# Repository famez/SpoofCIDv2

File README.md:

Project forked from https://github.com/spoofcid/spoofcid

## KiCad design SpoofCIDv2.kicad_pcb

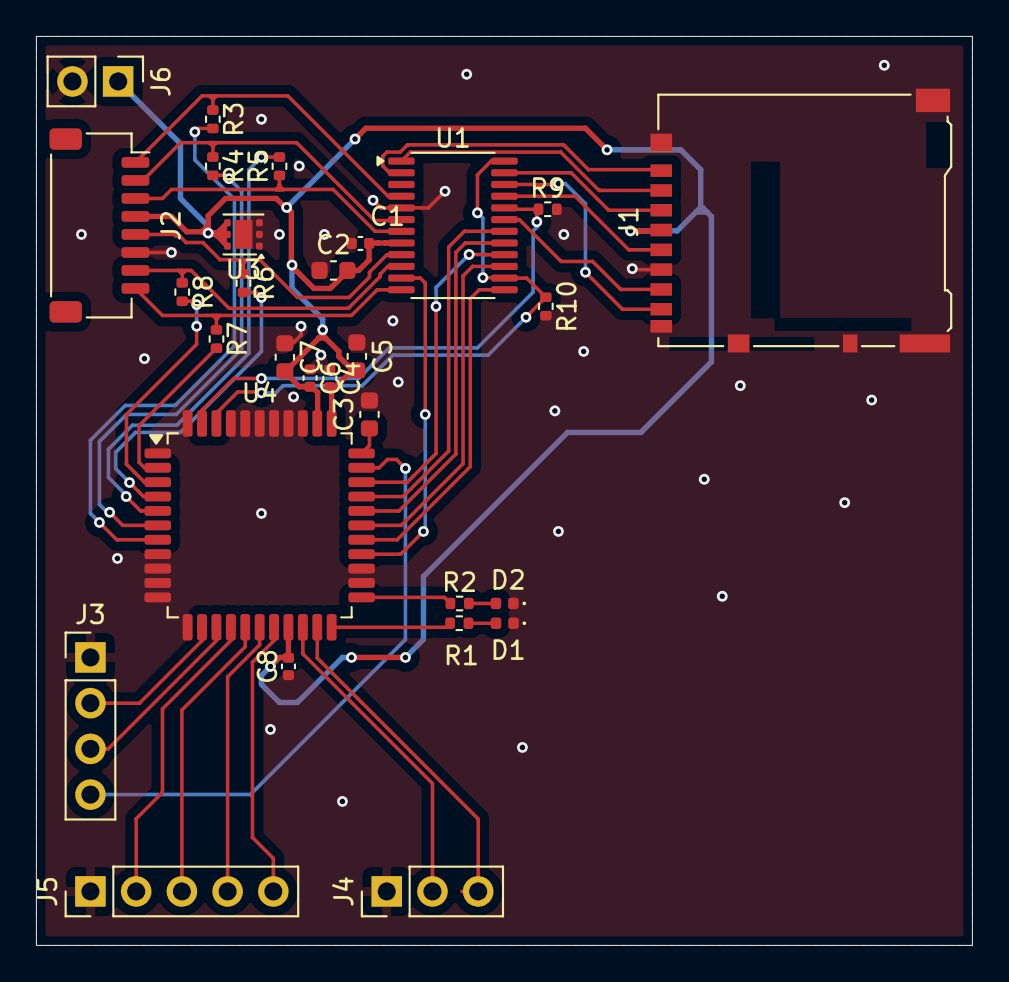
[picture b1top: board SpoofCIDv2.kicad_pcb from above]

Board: 2 copper layers, 52.0 x 50.5 mm, 29 parts (0 on the bottom side), 42 nets.

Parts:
C1, C4, C6, C8: 0.1u; C_0402_1005Metric
C2, C5, C7: 2.2u; C_0603_1608Metric
C3: 1.5u; C_0603_1608Metric
D1: GREEN LED; LED_0402_1005Metric
D2: RED LED; LED_0402_1005Metric
J1: Micro_SD_Card; microSD_HC_Hirose_DM3AT-SF-PEJM5
J2: Conn_01x08; JST_SH_SM08B-SRSS-TB_1x08-1MP_P1.00mm_Horizontal
J3: Conn_01x04_Pin; PinHeader_1x04_P2.54mm_Vertical
J4: Conn_01x03_Pin; PinHeader_1x03_P2.54mm_Vertical
J5: Conn_01x05_Pin; PinHeader_1x05_P2.54mm_Vertical
J6: Conn_01x02_Pin; PinHeader_1x02_P2.54mm_Vertical
R1, R3, R4, R5, R6, R7, R8: 100; R_0402_1005Metric
R2: 220; R_0402_1005Metric
R9, R10: 10k; R_0402_1005Metric
U1: TS3A27518EPW; TSSOP-24_4.4x7.8mm_P0.65mm
U3: TVS0500DRV; WSON-6-1EP_2x2mm_P0.65mm_EP1x1.6mm
U4: TQFP-44_10x10mm_P0.8mm

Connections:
+3.3V: C1.2, C2.2, C4.2, C5.2, C6.2, C7.2, C8.2, J1.4 (VDD), J2.4, J6.1, U1.8 (VCC), U3.4 (IN), U3.5 (IN), U3.6 (IN), U4.19 (VDDD), U4.34 (VDDD), U4.35 (VDDA)
/CARD_CLK: J1.5 (CLK), U1.21 (NC4)
/CARD_CMD: J1.3 (CMD), U1.23 (NC3)
/CARD_DAT0: J1.7 (DAT0), U1.19 (NC5)
/CARD_DAT1: J1.8 (DAT1), U1.22 (NC6)
/CARD_DAT2: J1.1 (DAT2), U1.2 (NC1)
/CARD_DAT3: J1.2 (DAT3/CD), U1.1 (NC2)
/HOST_CLK: J2.5, R6.1, U1.9 (COM4)
/HOST_CMD: J2.3, R5.1, U1.7 (COM3)
/HOST_DAT0: J2.7, R8.1, U1.10 (COM5)
/HOST_DAT1: J2.8, R7.1, U1.12 (COM6)
/HOST_DAT2: J2.1, R3.1, U1.4 (COM1)
/HOST_DAT3: J2.2, R4.1, U1.6 (COM2)
/PSOC_CLK: U1.17 (NO4), U4.29 (P0.5)
/PSOC_CMD: U1.15 (NO3), U4.28 (P0.4)
/PSOC_DAT0: U1.18 (NO5), U4.30 (P0.6)
/PSOC_DAT1: U1.16 (NO6), U4.31 (P0.7)
/PSOC_DAT2: U1.11 (NO1), U4.26 (P0.2)
/PSOC_DAT3: U1.13 (NO2), U4.27 (P0.3)
/SWDCLK: J3.3, U4.14 (P3.3)
/SWDIO: J3.2, U4.13 (P3.2)
/UART_RX: J4.2, U4.20 (P4.0)
/UART_TX: J4.3, U4.21 (P4.1)
/XRESET: J3.4, U4.32 (XRES)
GND: C1.1, C2.1, C3.2, C4.1, C5.1, C6.1, C7.1, C8.1, D1.1 (K), D2.1 (K), J1.6 (VSS), J1.9 (SHIELD), J1.10, J1.11, J2.6, J3.1, J4.1, J5.1, J6.2, R9.2, R10.2, U1.5 (GND), U3.1 (GND), U3.2 (GND), U3.3 (GND), U3.7 (GND), U4.1 (VSS), U4.8 (P2.6), U4.9 (P2.7), U4.10 (VSS), U4.11 (P3.0), U4.12 (P3.1), U4.24 (P0.0), U4.25 (P0.1), U4.36 (VSSA), U4.37 (P1.0), U4.38 (P1.1), U4.39 (P1.2), U4.40 (P1.3), U4.41 (P1.4), U4.44 (P1.7)
unnamed: D1.2 (A), R1.2
unnamed: D2.2 (A), R2.2
unnamed: J5.2, U4.15 (P3.4)
unnamed: J5.3, U4.16 (P3.5)
unnamed: J5.4, U4.17 (P3.6)
unnamed: J5.5, U4.18 (P3.7)
unnamed: R10.1, U1.14 (IN2), U1.24 (IN1), U4.42 (P1.5)
unnamed: R9.1, U1.20 (~EN), U4.43 (P1.6)
unnamed: R7.2, U4.2 (P2.0)
unnamed: R8.2, U4.3 (P2.1)
unnamed: R6.2, U4.4 (P2.2)
unnamed: R5.2, U4.5 (P2.3)
unnamed: R4.2, U4.6 (P2.4)
unnamed: R3.2, U4.7 (P2.5)
unnamed: R1.1, U4.22 (P4.2)
unnamed: R2.1, U4.23 (P4.3)
unnamed: C3.1, U4.33 (VCCD)

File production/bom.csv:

Designator,Footprint,Quantity,Value,LCSC Part #
"C1, C4, C6, C8",0402,4,0.1u,
"C2, C5, C7",0603,3,2.2u,
C3,0603,1,1.5u,
D1,0402,1,GREEN LED,
D2,0402,1,RED LED,
J1,microSD_HC_Hirose_DM3AT-SF-PEJM5,1,Micro_SD_Card,
J2,JST_SH_SM08B-SRSS-TB_1x08-1MP_P1.00mm_Horizontal,1,Conn_01x08,
J3,PinHeader_1x04_P2.54mm_Vertical,1,Conn_01x04_Pin,
J4,PinHeader_1x03_P2.54mm_Vertical,1,Conn_01x03_Pin,
J5,PinHeader_1x05_P2.54mm_Vertical,1,Conn_01x05_Pin,
J6,PinHeader_1x02_P2.54mm_Vertical,1,Conn_01x02_Pin,
"R1, R3, R4, R5, R6, R7, R8",0402,7,100,
"R10, R9",0402,2,10k,
R2,0402,1,220,
U1,TSSOP-24_4.4x7.8mm_P0.65mm,1,TS3A27518EPW,
U3,WSON-6-1EP_2x2mm_P0.65mm_EP1x1.6mm,1,TVS0500DRV,
U4,TQFP-44_10x10mm_P0.8mm,1,~,
